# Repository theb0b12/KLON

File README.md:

# KLON
## A CLONE of Geist's Klor

- Choc + MX hotswap (at the same time on the board)
- wired and wireless support
- reversible
- rotary support
- nice!view support along with the normal OLED display
- breakaway pcb

#### Name
Clone + klor = klon

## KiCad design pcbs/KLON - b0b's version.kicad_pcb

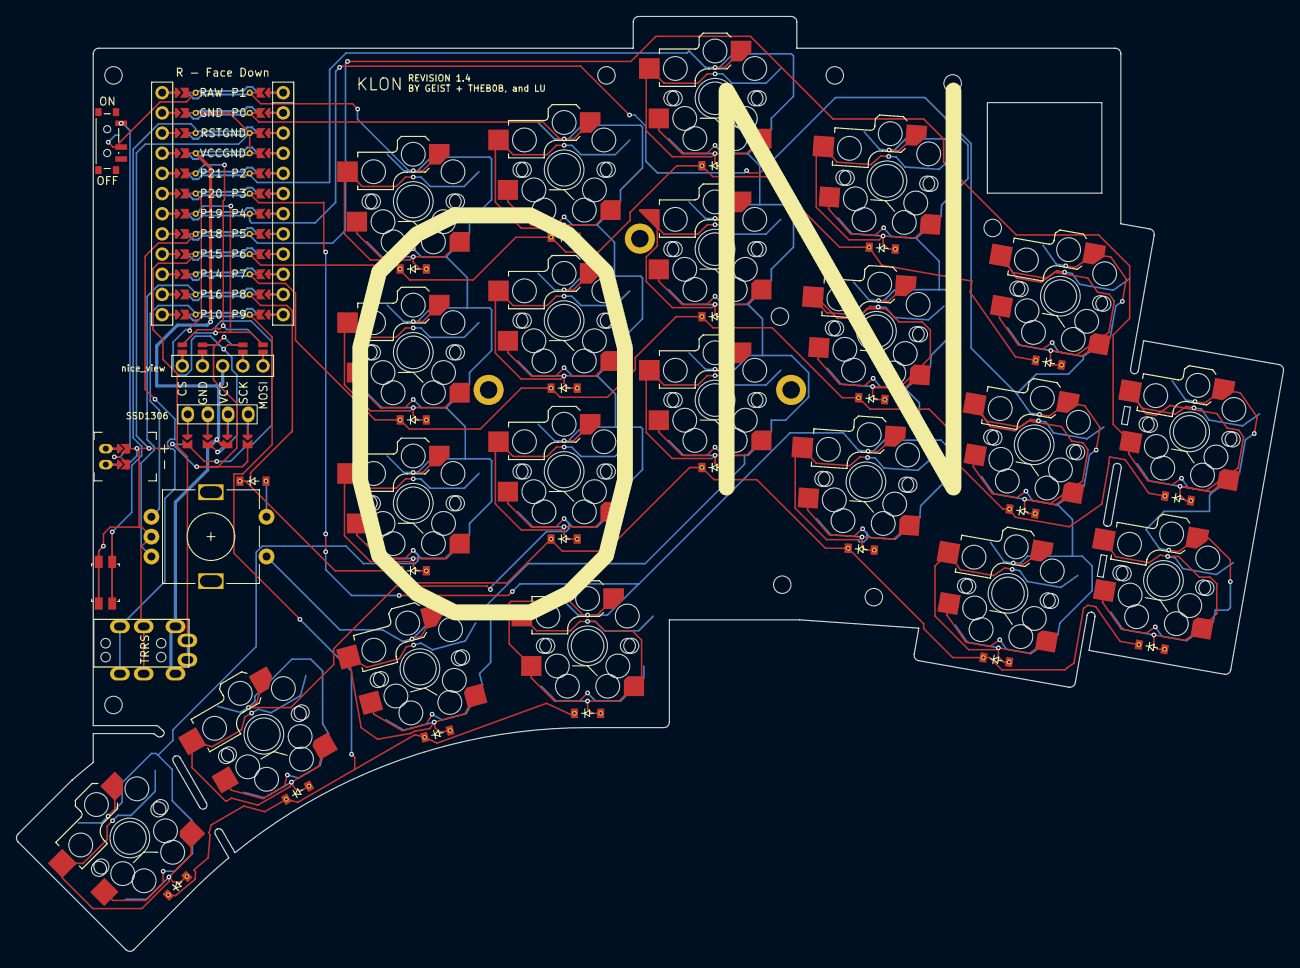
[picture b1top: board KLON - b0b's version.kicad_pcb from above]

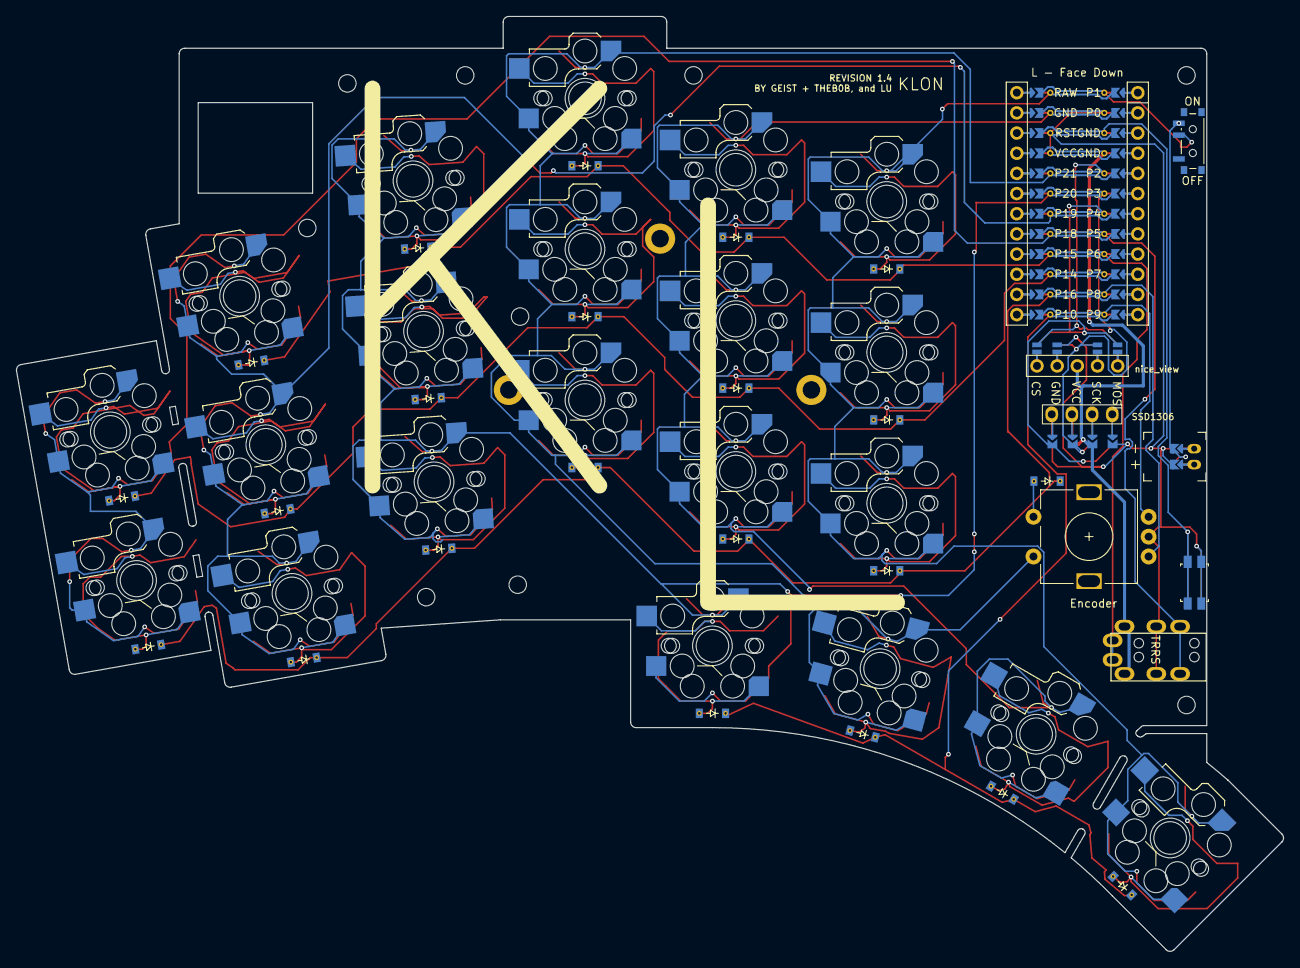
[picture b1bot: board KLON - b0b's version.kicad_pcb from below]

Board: 2 copper layers, 159.6 x 117.7 mm, 88 parts (42 on the bottom side), 54 nets.

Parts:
D1, D2, D3, D4, D5, D6, D7, D8, D9, D10, D11, D12, D13, D14, D15, D16, D17, D18, D19, D20, D21, D22: ComboDiode
DISP1: display_nice_view
H1, H2, H3: mounting_hole_plated
J1: MJ-4PP-9
JST1: battery_connector_jst_ph_2
MCU1: mcu_nice_nano
MH1, MH2, MH3, MH4, MH5, MH6, MH7, MH8, MH9: mounting_hole_npth
PWR1: power_switch_smd_side
RST1: reset_switch_smd_side
S1, S2, S3, S4, S5, S6, S7, S8, S9, S10, S11, S12, S13, S14, S15, S16, S17, S18, S19, S20, S21: switch_choc_v1_v2
S22, S23, S24, S25, S26, S27, S28, S29, S30, S31, S32, S33, S34, S35, S36, S37, S38, S39, S40, S41, S42: switch_mx
SSD1306: SSD1306_128x64OLED
SW25: Rotary_Encoder_Switch; RotaryEncoder_Alps_EC11E-Switch_Vertical_H20mm-keebio_modif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
XX4, XX5, XX6, XX7: jumper

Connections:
1_r0: D18.1, D18.2, S18.2, S39.2
2_r0: D19.1, D19.2, S19.2, S40.2
3_r0: D20.1, D20.2, S20.2, S41.2
4_r0: D21.1, D21.2, S21.2, S42.2
BAT_P: JST1.1, PWR1.1, PWR1.3
CS: DISP1.14, DISP1.24, MCU1.120
DISP1_1: DISP1.1, DISP1.10, DISP1.23
DISP1_2: DISP1.2, DISP1.11, DISP1.22
DISP1_4: DISP1.4, DISP1.12, DISP1.21
DISP1_5: DISP1.5, DISP1.13, DISP1.20
GND: DISP1.15, DISP1.25, J1.2, JST1.2, MCU1.103, MCU1.104, MCU1.123, RST1.1, RST1.3, SW25.C, XX4.2, XX7.2
JST1_1: JST1.11, JST1.21, JST1.31
JST1_2: JST1.12, JST1.22, JST1.32
MOSI: DISP1.17, DISP1.27, MCU1.118, XX4.2, XX7.2
P10: MCU1.113, SW25.A
P15: J1.4, MCU1.116
P16: MCU1.114, SW25.B
P18: J1.3, MCU1.117
RAW: MCU1.124, PWR1.2
RST: MCU1.122, RST1.2, RST1.4
SCK: DISP1.16, DISP1.26, MCU1.119, XX5.2, XX6.2
SW18B: D22.1, D22.2, SW25.S2
VCC: DISP1.3, J1.1, MCU1.121, XX5.2, XX6.2
col1: MCU1.101, S1.1, S2.1, S3.1, S21.1, S22.1, S23.1, S24.1, S42.1
col2: MCU1.102, S4.1, S5.1, S6.1, S20.1, S25.1, S26.1, S27.1, S41.1
col3: MCU1.105, S7.1, S8.1, S9.1, S19.1, S28.1, S29.1, S30.1, S40.1, SW25.S1
col4: MCU1.106, S10.1, S11.1, S12.1, S18.1, S31.1, S32.1, S33.1, S39.1
col5: MCU1.107, S13.1, S14.1, S15.1, S34.1, S35.1, S36.1
col6: MCU1.108, S16.1, S17.1, S37.1, S38.1
dis1-pad1: SSD1306.4, XX4.1
dis1-pad2: SSD1306.3, XX5.1
dis1-pad3: SSD1306.2, XX6.1
dis1-pad4: SSD1306.1, XX7.1
index_bottom: D4.1, D4.2, S4.2, S25.2
index_home: D5.1, D5.2, S5.2, S26.2
index_top: D6.1, D6.2, S6.2, S27.2
inner_bottom: D1.1, D1.2, S1.2, S22.2
inner_home: D2.1, D2.2, S2.2, S23.2
inner_top: D3.1, D3.2, S3.2, S24.2
middle_bottom: D7.1, D7.2, S7.2, S28.2
middle_home: D8.1, D8.2, S8.2, S29.2
middle_top: D9.1, D9.2, S9.2, S30.2
pinky_bottom: D13.1, D13.2, S13.2, S34.2
pinky_extra_bottom: D16.1, D16.2, S16.2, S37.2
pinky_extra_home: D17.1, D17.2, S17.2, S38.2
pinky_home: D14.1, D14.2, S14.2, S35.2
pinky_top: D15.1, D15.2, S15.2, S36.2
ring_bottom: D10.1, D10.2, S10.2, S31.2
ring_home: D11.1, D11.2, S11.2, S32.2
ring_top: D12.1, D12.2, S12.2, S33.2
row1: D3.1, D6.1, D9.1, D12.1, D15.1, MCU1.109
row2: D2.1, D5.1 (row2), D8.1 (row2), D11.1 (row2), D14.1 (row2), D17.1 (row2), MCU1.110
row3: D1.1, D4.1, D7.1, D10.1, D13.1, D16.1, D22.1, MCU1.111
row4: D18.1, D19.1, D20.1, D21.1, MCU1.112

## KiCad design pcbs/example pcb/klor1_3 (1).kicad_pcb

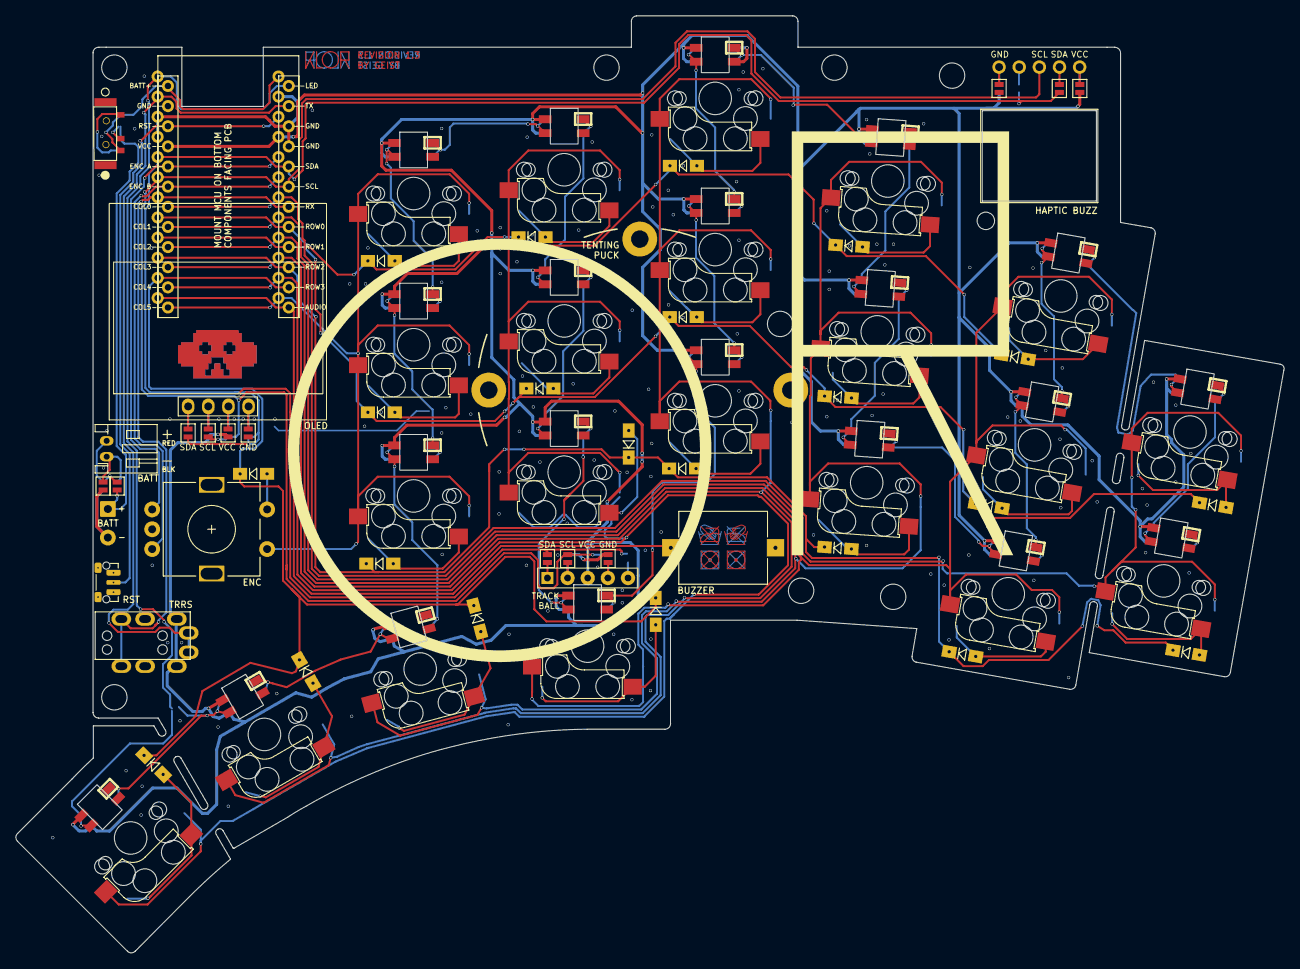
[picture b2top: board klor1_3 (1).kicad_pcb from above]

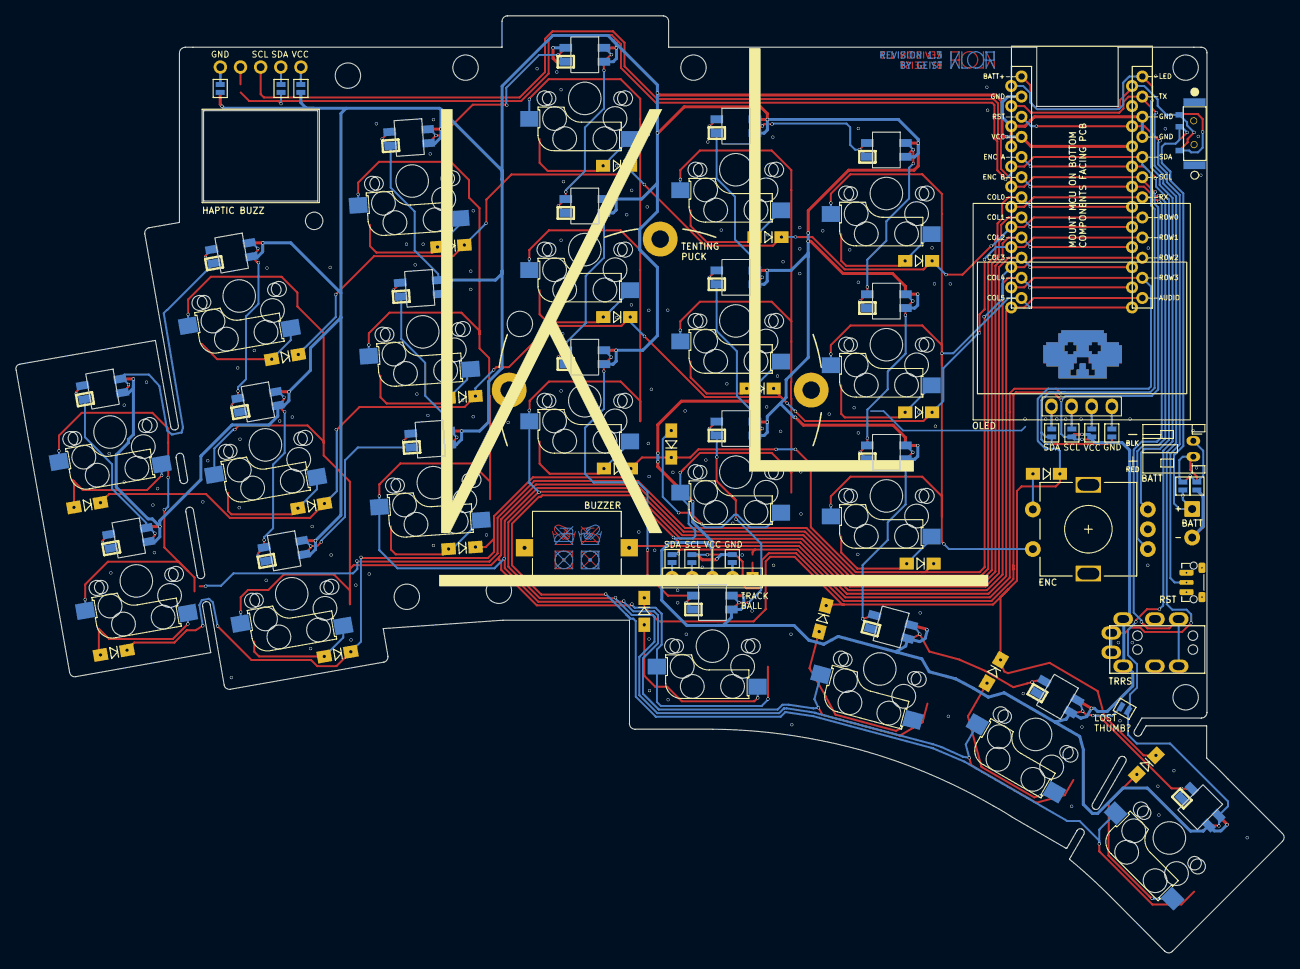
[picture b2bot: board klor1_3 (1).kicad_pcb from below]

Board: 2 copper layers, 160.0 x 118.2 mm, 88 parts (14 on the bottom side), 79 nets.

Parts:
BT1: JST Connector; JST_PH_reversible
BT2: Battery_Cell; custombatteryconnector_small
BZ1: Buzzer; Buzzer_Mallory_AST1109MLTRQ_reversible
D1, D2, D3, D4, D5, D6, D7, D8, D9, D10, D11, D12, D13, D14, D15, D16, D17, D18, D19, D20, D21, D22: D_Small; Diode_SOD123
J1: MJ-4PP-9
J2: Haptic Buzz; Pimoroni Haptic Buzz DRV2605L Driver
J3: lv27; lvc27_onlyInput
JP1, JP2, JP3, JP4, JP5, JP6, JP7, JP8, JP16, JP17, JP18, JP19, JP20, JP21, JP22, JP23, JP24, JP25, JP26, JP27, JP28: Device_Jumper_NO_Small; Jumper
JP12, JP14: VCC Jumper; Jumper
JP13, JP15: GND Jumper; Jumper
MH1, MH2, MH3, MH4, MH5, MH6, MH7, MH8: MountingHole_3.2mm_M3
MH9: MountingHole_2.2mm_M2
OLED1: SSD1306; SSD1306_128x64OLED
PSW1: SW_DPDT_x2; MSK12C02_reversible
RSW1: SW_Push; SW_Push_1P1T-MP_NO_Horizontal_Alps_SKRTLAE010_both_sides
SW1, SW2, SW3, SW4, SW5, SW6, SW7, SW8, SW9, SW10, SW11, SW12, SW13, SW14, SW15, SW16, SW17, SW19, SW20, SW21, SW22: SW_PUSH-MX_W_LED; SK6812MINI_and_cherry
SW18: RotaryEncoder_Switch; RotaryEncoder_Alps_EC11E-Switch_Vertical_H20mm-keebio_modif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
U1: ProMicro

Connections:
+BATT: PSW1.3 (C), U1.24 (RAW)
/PAD1: BT1.1 (+), JP22.1, JP23.1
/PAD2: BT1.2 (-), JP24.1, JP25.1
/PSW: BT2.1 (+), JP23.2, JP24.2, PSW1.2 (B)
AUDIO: BZ1.1 (-), U1.12 (9/B5)
ENCA: SW18.A, U1.20 (F4/A3)
ENCB: SW18.B, U1.19 (F5/A2)
GND: BT2.2 (-), BZ1.2 (+), J1.2, JP1.2, JP8.2, JP13.1 (A), JP15.1 (A), JP18.2, JP19.2, JP22.2, JP25.2, RSW1.1, SW1.2 (VSS), SW2.2 (VSS), SW3.2 (VSS), SW4.2 (VSS), SW5.2 (VSS), SW6.2 (VSS), SW7.2 (VSS), SW8.2 (VSS), SW9.2 (VSS), SW10.2 (VSS), SW11.2 (VSS), SW12.2 (VSS), SW13.2 (VSS), SW14.2 (VSS), SW15.2 (VSS), SW16.2 (VSS), SW17.2 (VSS), SW18.C, SW19.2 (VSS), SW20.2 (VSS), SW21.2 (VSS), SW22.2 (VSS), U1.3 (GND), U1.4 (GND), U1.23 (GND)
LED: JP26.2, SW19.3 (DIN), U1.1 (TX0/D3)
unnamed: D1.2 (A), SW1.6
unnamed: D2.2 (A), SW2.6
unnamed: D3.2 (A), SW3.6
unnamed: D4.2 (A), SW4.6
unnamed: D5.2 (A), SW5.6
unnamed: D6.2 (A), SW6.6
unnamed: D7.2 (A), SW7.6
unnamed: D8.2 (A), SW8.6
unnamed: D9.2 (A), SW9.6
unnamed: D10.2 (A), SW10.6
unnamed: D11.2 (A), SW11.6
unnamed: D12.2 (A), SW12.6
unnamed: D13.2 (A), SW13.6
unnamed: D14.2 (A), SW14.6
unnamed: D15.2 (A), SW15.6
unnamed: D16.2 (A), SW16.6
unnamed: D17.2 (A), SW17.6
unnamed: D19.2 (A), SW19.6
unnamed: D20.2 (A), SW20.6
unnamed: D21.2 (A), SW21.6
unnamed: D22.2 (A), SW22.6
unnamed: J2.1, JP12.2 (B), JP13.2 (B)
unnamed: J2.2, JP27.2
unnamed: J2.4, JP28.2
unnamed: J2.5, JP14.2 (B), JP15.2 (B)
unnamed: J3.1, JP16.1
unnamed: J3.2, JP17.1, JP19.1
unnamed: J3.4, JP18.1, JP20.1
unnamed: J3.5, JP21.1
unnamed: JP1.1, JP5.1, OLED1.1 (GND)
unnamed: JP2.1, JP6.1, OLED1.2 (VCC)
unnamed: JP3.1, JP7.1, OLED1.3 (SCL)
unnamed: JP4.1, JP8.1, OLED1.4 (SDA)
unnamed: JP26.1, SW19.1 (DOUT), SW20.3 (DIN)
unnamed: SW1.1 (DOUT), SW2.3 (DIN)
unnamed: SW1.3 (DIN), SW6.1 (DOUT)
unnamed: SW2.1 (DOUT), SW7.3 (DIN)
unnamed: SW3.1 (DOUT), SW4.3 (DIN)
unnamed: SW3.3 (DIN), SW8.1 (DOUT)
unnamed: SW4.1 (DOUT), SW9.3 (DIN)
unnamed: SW5.3 (DIN), SW10.1 (DOUT)
unnamed: SW10.3 (DIN), SW16.1 (DOUT)
unnamed: SW11.1 (DOUT), SW17.3 (DIN)
unnamed: SW5.1 (DOUT), SW11.3 (DIN)
unnamed: SW6.3 (DIN), SW12.1 (DOUT)
unnamed: SW12.3 (DIN), SW21.1 (DOUT)
unnamed: SW13.1 (DOUT), SW22.3 (DIN)
unnamed: SW7.1 (DOUT), SW13.3 (DIN)
unnamed: SW8.3 (DIN), SW14.1 (DOUT)
unnamed: SW14.3 (DIN), SW22.1 (DOUT)
unnamed: SW15.1 (DOUT), SW16.3 (DIN)
unnamed: SW9.1 (DOUT), SW15.3 (DIN)
unnamed: SW20.1 (DOUT), SW21.3 (DIN)
RESET: RSW1.2, U1.22 (RST)
RX: J1.3, U1.7 (4/D4)
SCL: J2.3, JP3.2, JP6.2, JP17.2, JP20.2, U1.6 (3/D0/SCL)
SDA: JP4.2, JP5.2, JP16.2, JP21.2, JP27.1, JP28.1, U1.5 (2/D1/SDA)
SW18B: D18.2 (A), SW18.S2
TX: J1.4, U1.2 (RX1/D2)
VCC: J1.1, J3.3, JP2.2, JP7.2, JP12.1 (A), JP14.1 (A), SW1.4 (VDD), SW2.4 (VDD), SW3.4 (VDD), SW4.4 (VDD), SW5.4 (VDD), SW6.4 (VDD), SW7.4 (VDD), SW8.4 (VDD), SW9.4 (VDD), SW10.4 (VDD), SW11.4 (VDD), SW12.4 (VDD), SW13.4 (VDD), SW14.4 (VDD), SW15.4 (VDD), SW16.4 (VDD), SW17.4 (VDD), SW19.4 (VDD), SW20.4 (VDD), SW21.4 (VDD), SW22.4 (VDD), U1.21 (VCC)
col0: SW11.5, SW17.5, U1.18 (F6/A1)
col1: SW5.5, SW10.5, SW16.5, SW22.5, U1.17 (F7/A0)
col2: SW4.5, SW9.5, SW15.5, SW21.5, U1.16 (B1/15)
col3: SW3.5, SW8.5, SW14.5, SW20.5, U1.15 (B3/14)
col4: SW2.5, SW7.5, SW13.5, SW19.5, U1.14 (B2/16)
col5: SW1.5, SW6.5, SW12.5, SW18.S1, U1.13 (B6/10)
row0: D1.1 (K), D2.1 (K), D3.1 (K), D4.1 (K), D5.1 (K), U1.8 (5/C6)
row1: D6.1 (K), D7.1 (K), D8.1 (K), D9.1 (K), D10.1 (K), D11.1 (K), U1.9 (6/D7)
row2: D12.1 (K), D13.1 (K), D14.1 (K), D15.1 (K), D16.1 (K), D17.1 (K), U1.10 (7/E6)
row3: D18.1 (K), D19.1 (K), D20.1 (K), D21.1 (K), D22.1 (K), U1.11 (8/B4)

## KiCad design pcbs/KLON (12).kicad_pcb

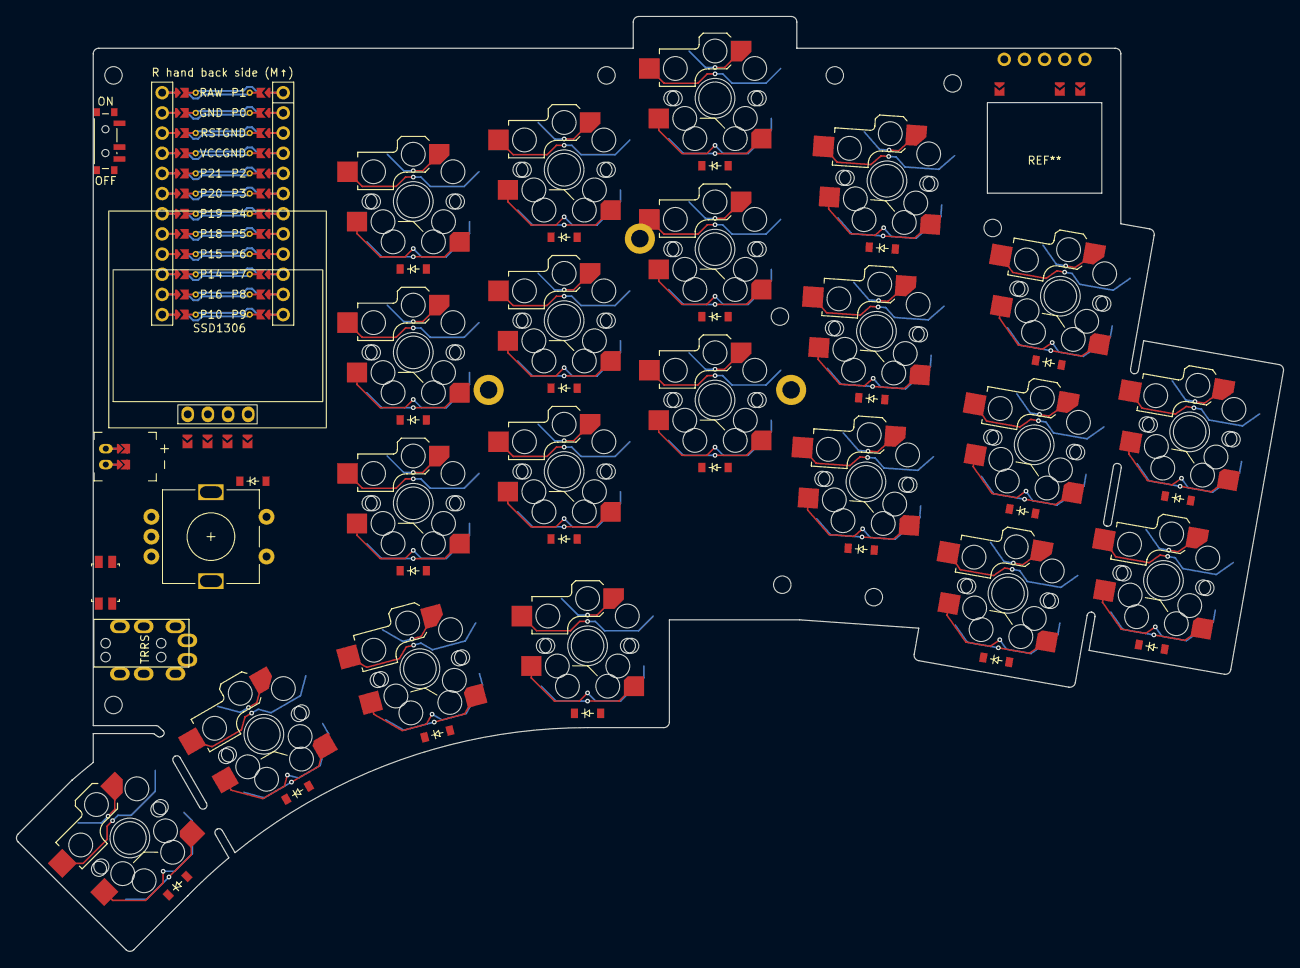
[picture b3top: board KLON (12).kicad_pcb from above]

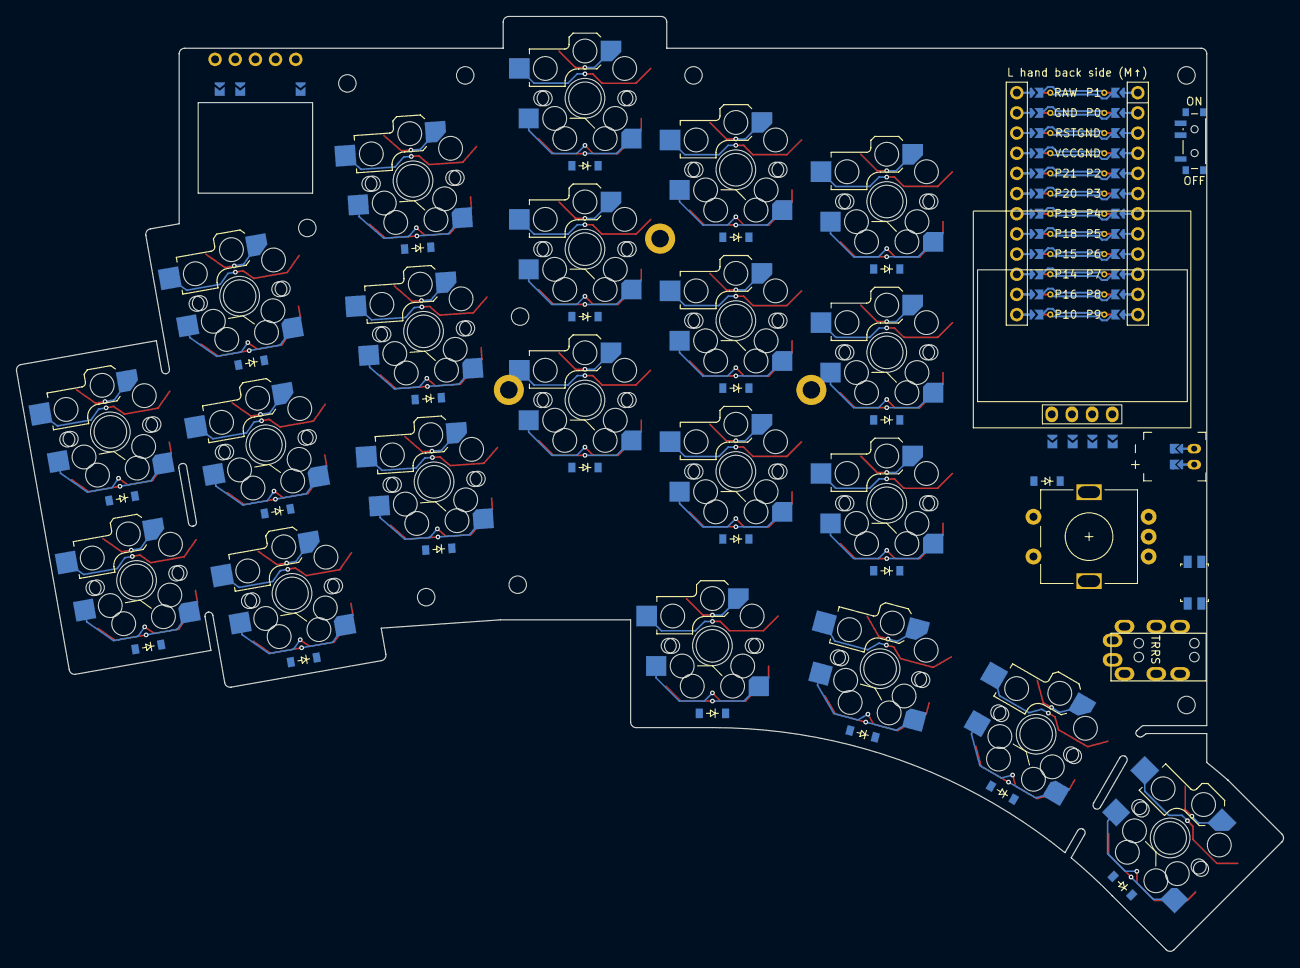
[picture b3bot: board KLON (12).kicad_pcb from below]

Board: 2 copper layers, 159.6 x 117.7 mm, 90 parts (42 on the bottom side), 40 nets.

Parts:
D1, D2, D3, D4, D5, D6, D7, D8, D9, D10, D11, D12, D13, D14, D15, D16, D17, D18, D19, D20, D21, D22: diode_tht_sod123
H1, H2, H3: mounting_hole_plated
J1: MJ-4PP-9
JST1: battery_connector_jst_ph_2
MCU1: mcu_nice_nano
MH1, MH2, MH3, MH4, MH5, MH6, MH7, MH8, MH9: mounting_hole_npth
PWR1: power_switch_smd_side
RST1: reset_switch_smd_side
S1, S2, S3, S4, S5, S6, S7, S8, S9, S10, S11, S12, S13, S14, S15, S16, S17, S18, S19, S20, S21: switch_choc_v1_v2
S22, S23, S24, S25, S26, S27, S28, S29, S30, S31, S32, S33, S34, S35, S36, S37, S38, S39, S40, S41, S42: switch_mx
SSD1306: SSD1306_128x64OLED
SW25: Rotary_Encoder_Switch; RotaryEncoder_Alps_EC11E-Switch_Vertical_H20mm-keebio_modif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
XX5, XX6, XX7, XX8, XX9, XX10, XX11: jumper

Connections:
1_r0: D18.2, S18.2, S39.2
2_r0: D19.2, S19.2, S40.2
3_r0: D20.2, S20.2, S41.2
4_r0: D21.2, S21.2, S42.2
BAT_P: JST1.1, PWR1.1, PWR1.3
GND: J1.2, JST1.2, MCU1.103, MCU1.104, MCU1.123, RST1.1, RST1.3, SSD1306.1, SW25.C
JST1_1: JST1.11, JST1.21, JST1.31
JST1_2: JST1.12, JST1.22, JST1.32
P0: D1.1, D4.1, D7.1, D10.1, D13.1, D16.1, MCU1.102
P1: D2.1, D5.1, D8.1, D11.1, D14.1, D17.1, D22.1, MCU1.101, XX5.2, XX6.2, XX7.2, XX8.2, XX9.2, XX10.2, XX11.2
P2: D3.1, D6.1, D9.1, D12.1, D15.1, D22.2, MCU1.105, XX5.1, XX6.1, XX7.1, XX8.1, XX9.1, XX10.1, XX11.1
P3: MCU1.106, S1.1, S2.1, S3.1, S19.1, S22.1, S23.1, S24.1, S40.1
P4: MCU1.107, S4.1, S5.1, S6.1, S18.1, S25.1, S26.1, S27.1, S39.1
P5: MCU1.108, S7.1, S8.1, S9.1, S28.1, S29.1, S30.1
P6: MCU1.109, S10.1, S11.1, S12.1, S31.1, S32.1, S33.1
P7: MCU1.110, S13.1, S14.1, S15.1, S34.1, S35.1, S36.1
P8: MCU1.111, S16.1, S17.1, S37.1, S38.1
P9: D18.1, D19.1, D20.1, D21.1, MCU1.112
P10: MCU1.113, S20.1, S41.1
P16: MCU1.114, S21.1, S42.1
RAW: MCU1.124, PWR1.2
RST: MCU1.122, RST1.2, RST1.4
VCC: J1.1, MCU1.121, SSD1306.2
index_bottom: D4.2, S4.2, S25.2
index_home: D5.2, S5.2, S26.2
index_top: D6.2, S6.2, S27.2
inner_bottom: D1.2, S1.2, S22.2
inner_home: D2.2, S2.2, S23.2
inner_top: D3.2, S3.2, S24.2
middle_bottom: D7.2, S7.2, S28.2
middle_home: D8.2, S8.2, S29.2
middle_top: D9.2, S9.2, S30.2
pinky_bottom: D13.2, S13.2, S34.2
pinky_extra_bottom: D16.2, S16.2, S37.2
pinky_extra_home: D17.2, S17.2, S38.2
pinky_home: D14.2, S14.2, S35.2
pinky_top: D15.2, S15.2, S36.2
ring_bottom: D10.2, S10.2, S31.2
ring_home: D11.2, S11.2, S32.2
ring_top: D12.2, S12.2, S33.2

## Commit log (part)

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2026-04-10 Create README with project overview
    Add initial README content for Geist's Klor version.
2026-04-13 Revise README for Geist's Klor version
    Updated project title and features list in README.
2026-04-14 changed some stuff
2026-04-15 Update config(7).yaml
    completed outline, added breakaways
    TODO:
    mounting holes, everything else
2026-04-15 Modify starting coordinates and add PCB configurations
    Updated starting coordinates for KiCAD placement and added new PCB configurations.
2026-04-18 Modify shift values and add rotary encoder config
    Updated shift values for rectangle and haptic adjustments, and added rotary encoder configuration.
2026-04-18 Revise feature list in README
    Updated feature list with new items and formatting changes.
2026-04-18 Update README with detailed feature descriptions
    Clarified features of the Klor version in README.
2026-04-18 Rename config(10).yaml to config.yaml
2026-04-18 Remove klor.yaml configuration file
2026-04-19 Fix rotary encoder configuration
    Renamed 'rotary_encoder' to 'rotatry_encoder' and updated its parameters.
2026-04-19 Modify adjustments for components and fix spelling
    Updated battery_connector and on_off_switch adjustments, corrected spelling of rotary_encoder.
2026-04-19 Add reversible parameter to config settings
    Added 'reversible: true' to reset_switch and adjust parameters.
2026-05-01 updated distances for PCB
2026-05-02 updated config.yaml
2026-05-06 updated config.yaml ; moved reset, rotary, and created ttrs
2026-05-07 added mounting holes
2026-05-07 added updated pcb and added nets to things
2026-05-07 updated updated pcb and added nets to things
2026-05-07 pcb changes
2026-05-07 little changes
2026-05-18 updated config.yaml; added jumpers and one diode
2026-05-18 added jumper1 footprint
2026-05-18 updated jumper1 with comments
2026-05-18 added row and column nets
2026-05-18 deleted unneeded files
2026-05-22 pcb updates
2026-05-22 updateed jumper and added that to pcb
2026-05-22 added another pcb
2026-05-22 deleted unneded old PCBS
2026-05-22 changed some pcb stuff
2026-06-07 added cases and switch plate
